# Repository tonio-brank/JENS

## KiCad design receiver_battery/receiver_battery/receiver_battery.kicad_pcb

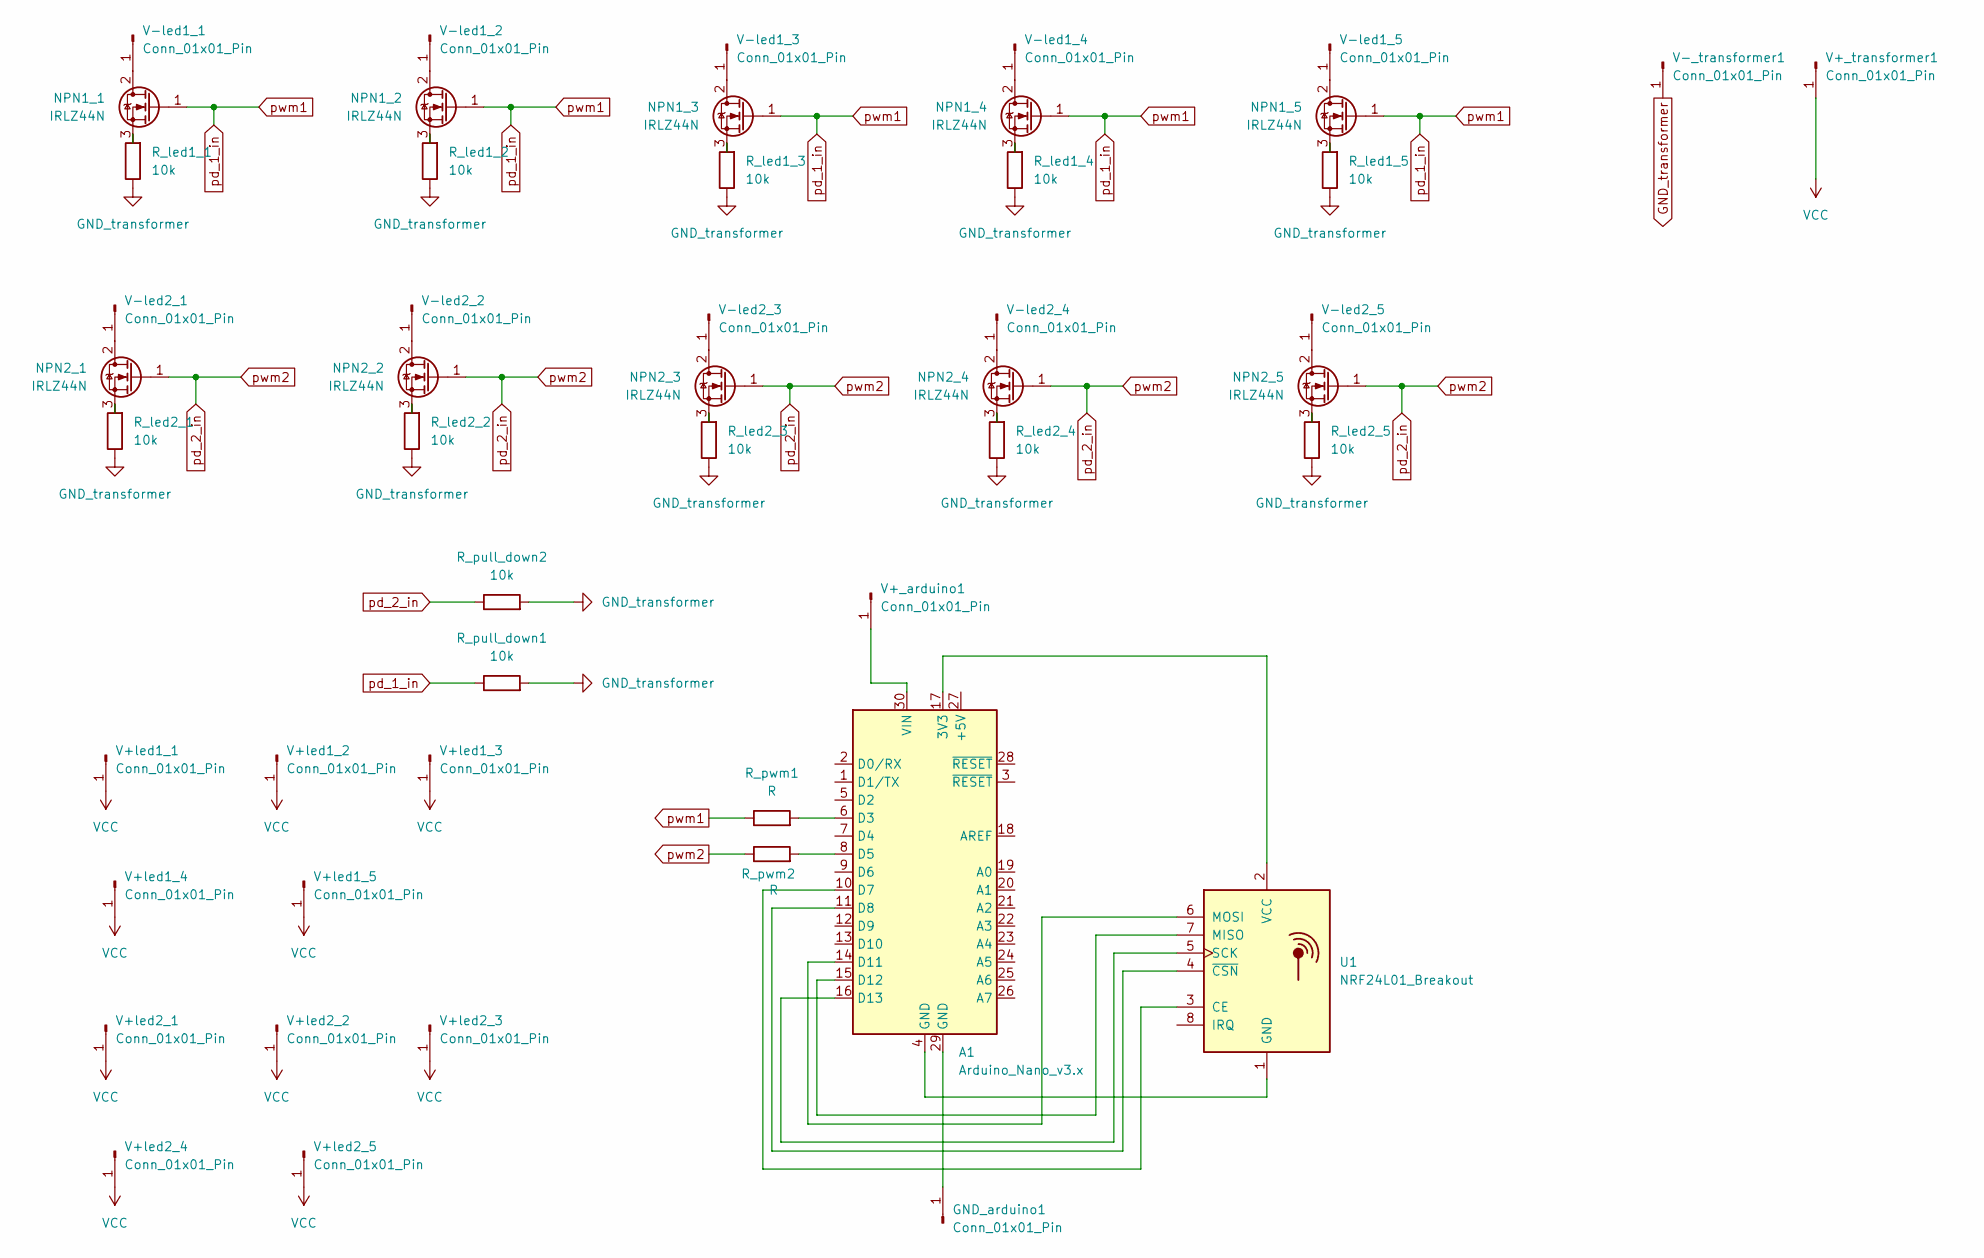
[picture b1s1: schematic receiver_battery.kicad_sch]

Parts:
A1: Arduino_Nano_v3.x; Arduino_Nano
GND_arduino1: Conn_01x01_Pin; SolderWire-1.5sqmm_1x01_D1.7mm_OD3.9mm
NPN1_1, NPN1_2, NPN1_3, NPN1_4, NPN1_5, NPN2_1, NPN2_2, NPN2_3, NPN2_4, NPN2_5: IRLZ44N; TO-220-3_Vertical
R_led1_1, R_led1_2, R_led1_3, R_led1_4, R_led1_5, R_led2_1, R_led2_2, R_led2_3, R_led2_4, R_led2_5: 10k; R_Axial_Power_L20.0mm_W6.4mm_P7.62mm_Vertical
R_pull_down1, R_pull_down2: 10k; R_Axial_DIN0207_L6.3mm_D2.5mm_P7.62mm_Horizontal
R_pwm1, R_pwm2: R; R_Axial_DIN0207_L6.3mm_D2.5mm_P7.62mm_Horizontal
U1: NRF24L01_Breakout; nRF24L01_Breakout
V+_arduino1: Conn_01x01_Pin; SolderWire-1.5sqmm_1x01_D1.7mm_OD3.9mm
V+_transformer1: Conn_01x01_Pin; SolderWire-1.5sqmm_1x01_D1.7mm_OD3.9mm
V+led1_1, V+led1_2, V+led1_3, V+led1_4, V+led1_5, V+led2_1, V+led2_2, V+led2_3, V+led2_4, V+led2_5: Conn_01x01_Pin; SolderWire-1.5sqmm_1x01_D1.7mm_OD3.9mm
V-_transformer1: Conn_01x01_Pin; SolderWire-1.5sqmm_1x01_D1.7mm_OD3.9mm
V-led1_1, V-led1_2, V-led1_3, V-led1_4, V-led1_5, V-led2_1, V-led2_2, V-led2_3, V-led2_4, V-led2_5: Conn_01x01_Pin; SolderWire-1.5sqmm_1x01_D1.7mm_OD3.9mm

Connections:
GND_transformer: R_led1_1.1, R_led1_2.1, R_led1_3.1, R_led1_4.1, R_led1_5.1, R_led2_1.1, R_led2_2.1, R_led2_3.1, R_led2_4.1, R_led2_5.1, R_pull_down1.2, R_pull_down2.2, V-_transformer1.1
unnamed: A1.17 (3V3), U1.2 (VCC)
unnamed: A1.6 (D3), R_pwm1.2
unnamed: A1.8 (D5), R_pwm2.2
unnamed: A1.10 (D7), U1.3 (CE)
unnamed: A1.11 (D8), U1.4 (~CSN)
unnamed: A1.14 (D11), U1.6 (MOSI)
unnamed: A1.15 (D12), U1.7 (MISO)
unnamed: A1.16 (D13), U1.5 (SCK)
unnamed: A1.30 (VIN), V+_arduino1.1
unnamed: A1.29 (GND), GND_arduino1.1
unnamed: NPN1_1.2 (D), V-led1_1.1
unnamed: NPN1_1.3 (S), R_led1_1.2
unnamed: NPN1_2.2 (D), V-led1_2.1
unnamed: NPN1_2.3 (S), R_led1_2.2
unnamed: NPN1_3.2 (D), V-led1_3.1
unnamed: NPN1_3.3 (S), R_led1_3.2
unnamed: NPN1_4.2 (D), V-led1_4.1
unnamed: NPN1_4.3 (S), R_led1_4.2
unnamed: NPN1_5.2 (D), V-led1_5.1
unnamed: NPN1_5.3 (S), R_led1_5.2
unnamed: NPN2_1.2 (D), V-led2_1.1
unnamed: NPN2_1.3 (S), R_led2_1.2
unnamed: NPN2_2.2 (D), V-led2_2.1
unnamed: NPN2_2.3 (S), R_led2_2.2
unnamed: NPN2_3.2 (D), V-led2_3.1
unnamed: NPN2_3.3 (S), R_led2_3.2
unnamed: NPN2_4.2 (D), V-led2_4.1
unnamed: NPN2_4.3 (S), R_led2_4.2
unnamed: NPN2_5.2 (D), V-led2_5.1
unnamed: NPN2_5.3 (S), R_led2_5.2
unnamed: A1.4 (GND), U1.1 (GND)
VCC: V+_transformer1.1, V+led1_1.1, V+led1_2.1, V+led1_3.1, V+led1_4.1, V+led1_5.1, V+led2_1.1, V+led2_2.1, V+led2_3.1, V+led2_4.1, V+led2_5.1
pd_1_in: NPN1_1.1 (G), NPN1_2.1 (G), NPN1_3.1 (G), NPN1_4.1 (G), NPN1_5.1 (G), R_pull_down1.1, R_pwm1.1
pd_2_in: NPN2_1.1 (G), NPN2_2.1 (G), NPN2_3.1 (G), NPN2_4.1 (G), NPN2_5.1 (G), R_pull_down2.1, R_pwm2.1

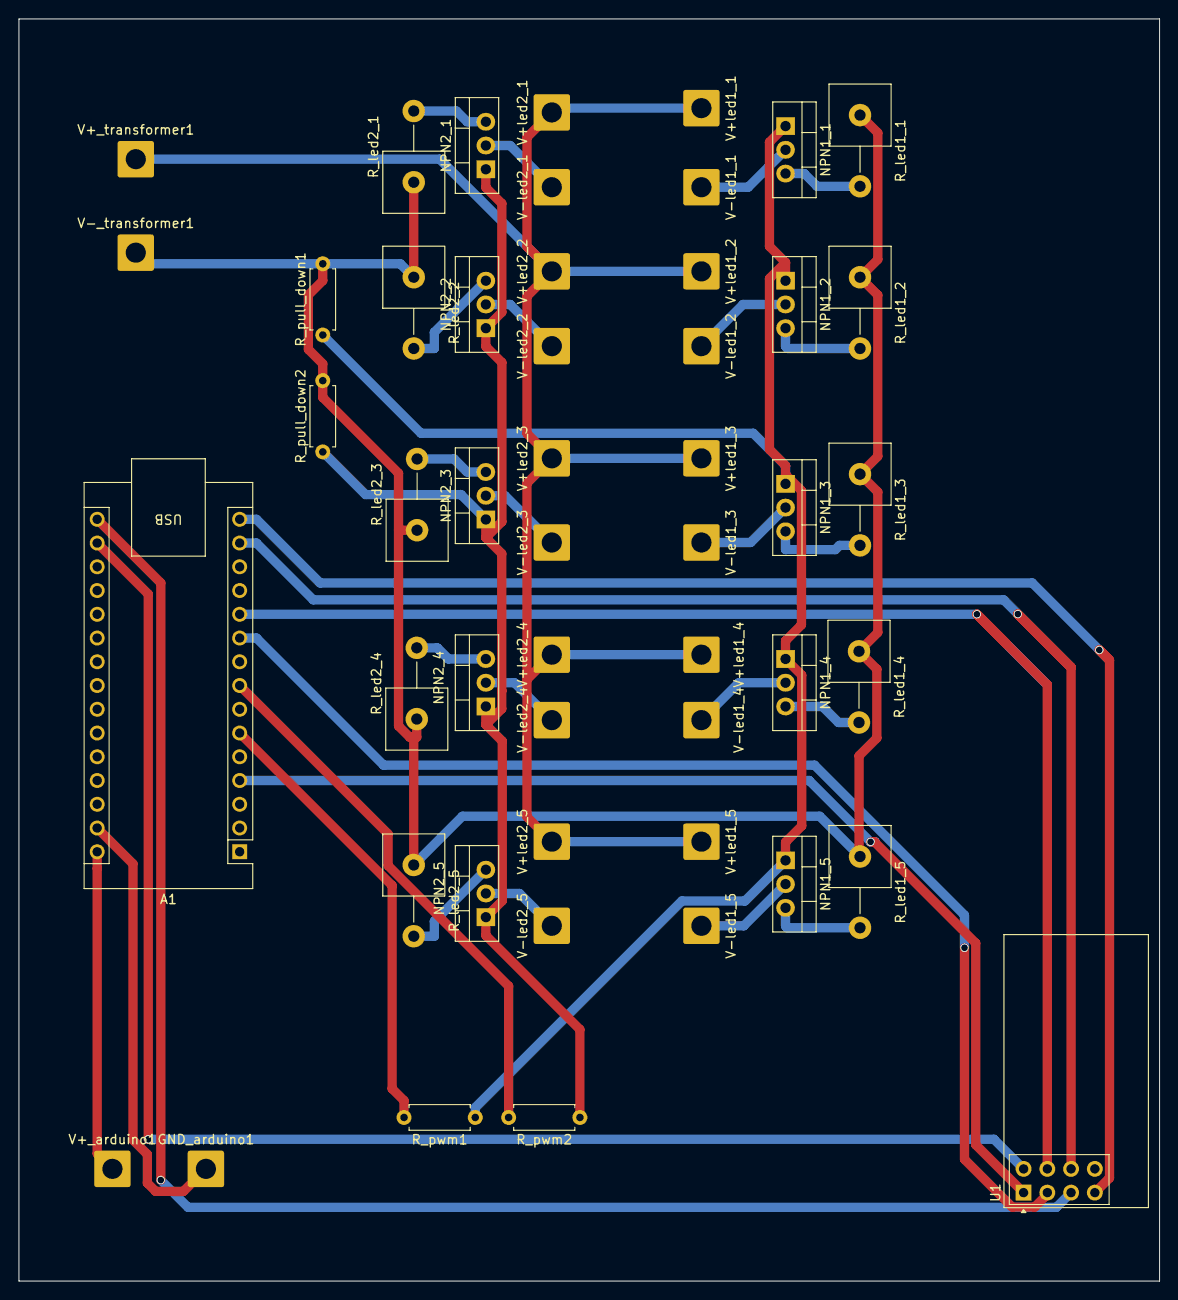
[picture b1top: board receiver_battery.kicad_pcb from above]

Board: 2 copper layers, 122.0 x 135.0 mm, 50 parts (0 on the bottom side), 35 nets.

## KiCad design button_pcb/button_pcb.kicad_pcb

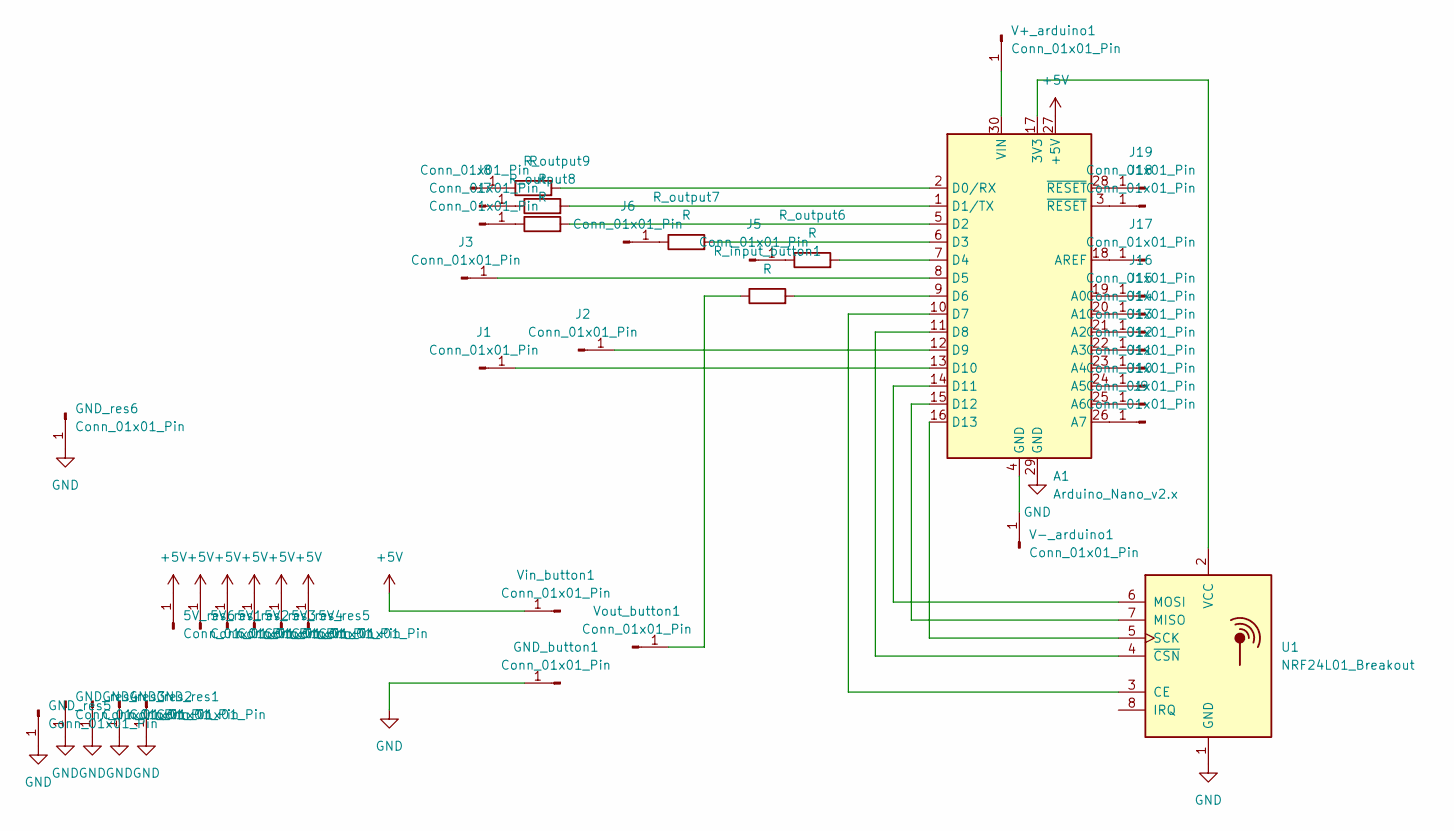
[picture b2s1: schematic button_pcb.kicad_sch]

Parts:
5V_res1, 5V_res2, 5V_res3, 5V_res4, 5V_res5, 5V_res6: Conn_01x01_Pin; SolderWire-0.75sqmm_1x01_D1.25mm_OD2.3mm
A1: Arduino_Nano_v2.x; Arduino_Nano
GND_button1: Conn_01x01_Pin; SolderWire-0.75sqmm_1x01_D1.25mm_OD2.3mm
GND_res1, GND_res2, GND_res3, GND_res4, GND_res5, GND_res6: Conn_01x01_Pin; SolderWire-0.75sqmm_1x01_D1.25mm_OD2.3mm
J1, J2, J3, J4, J5, J6, J7, J8, J9, J10, J11, J12, J13, J14, J15, J16, J17, J18, J19: Conn_01x01_Pin; SolderWire-0.75sqmm_1x01_D1.25mm_OD2.3mm
R_input_button1: R; R_Axial_DIN0207_L6.3mm_D2.5mm_P7.62mm_Horizontal
R_output5, R_output6, R_output7, R_output8, R_output9: R; R_Axial_DIN0207_L6.3mm_D2.5mm_P7.62mm_Horizontal
U1: NRF24L01_Breakout; nRF24L01_Breakout
V+_arduino1: Conn_01x01_Pin; SolderWire-0.75sqmm_1x01_D1.25mm_OD2.3mm
V-_arduino1: Conn_01x01_Pin; SolderWire-0.75sqmm_1x01_D1.25mm_OD2.3mm
Vin_button1: Conn_01x01_Pin; SolderWire-0.75sqmm_1x01_D1.25mm_OD2.3mm
Vout_button1: Conn_01x01_Pin; SolderWire-0.75sqmm_1x01_D1.25mm_OD2.3mm

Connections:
+5V: 5V_res1.1, 5V_res2.1, 5V_res3.1, 5V_res4.1, 5V_res5.1, 5V_res6.1, A1.27 (+5V), Vin_button1.1
GND: A1.29 (GND), GND_button1.1, GND_res1.1, GND_res2.1, GND_res3.1, GND_res4.1, GND_res5.1, GND_res6.1, U1.1 (GND)
unnamed: A1.17 (3V3), U1.2 (VCC)
unnamed: A1.19 (A0), J16.1
unnamed: A1.20 (A1), J15.1
unnamed: A1.21 (A2), J14.1
unnamed: A1.22 (A3), J13.1
unnamed: A1.23 (A4), J12.1
unnamed: A1.24 (A5), J11.1
unnamed: A1.25 (A6), J10.1
unnamed: A1.26 (A7), J9.1
unnamed: A1.18 (AREF), J17.1
unnamed: A1.2 (D0/RX), R_output5.2
unnamed: A1.1 (D1/TX), R_output9.2
unnamed: A1.5 (D2), R_output8.2
unnamed: A1.6 (D3), R_output7.2
unnamed: A1.7 (D4), R_output6.2
unnamed: A1.8 (D5), J3.1
unnamed: A1.9 (D6), R_input_button1.2
unnamed: A1.10 (D7), U1.3 (CE)
unnamed: A1.11 (D8), U1.4 (~CSN)
unnamed: A1.12 (D9), J2.1
unnamed: A1.13 (D10), J1.1
unnamed: A1.14 (D11), U1.6 (MOSI)
unnamed: A1.15 (D12), U1.7 (MISO)
unnamed: A1.16 (D13), U1.5 (SCK)
unnamed: A1.30 (VIN), V+_arduino1.1
unnamed: J4.1, R_output5.1
unnamed: J5.1, R_output6.1
unnamed: J6.1, R_output7.1
unnamed: J7.1, R_output8.1
unnamed: J8.1, R_output9.1
unnamed: A1.3 (~RESET), J18.1
unnamed: A1.28 (~RESET), J19.1
unnamed: A1.4 (GND), V-_arduino1.1
unnamed: R_input_button1.1, Vout_button1.1

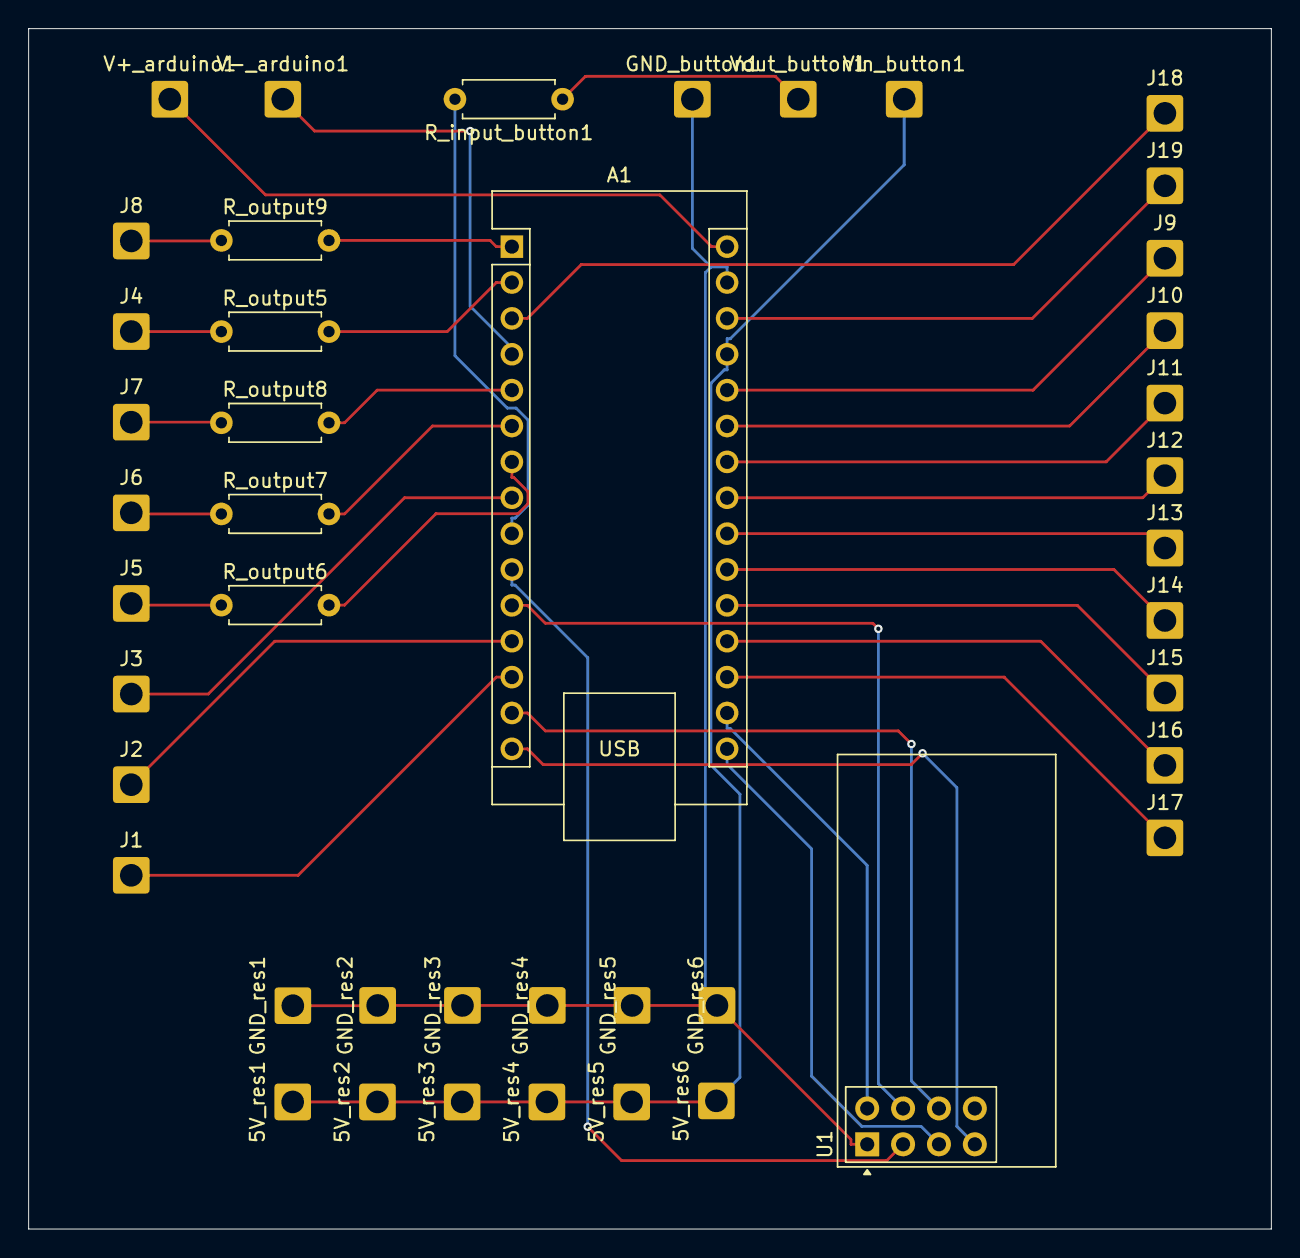
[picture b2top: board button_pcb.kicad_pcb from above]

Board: 2 copper layers, 88.0 x 85.0 mm, 44 parts (0 on the bottom side), 36 nets.

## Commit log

2025-05-09 pulldown on each transistor
2025-05-09 v0 ready for jlcpcb
2025-05-09 button pcb v0
2025-05-09 only 2 pull down res + res for each led
2025-05-09 large cock resistor
